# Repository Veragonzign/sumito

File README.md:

# sumito
Robot minisumo robtica tecnologia electrica

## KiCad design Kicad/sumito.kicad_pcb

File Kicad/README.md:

Esta carpeta contiene los archivos del esquema electrico y del diseño de la PCB del robot SUMITO.

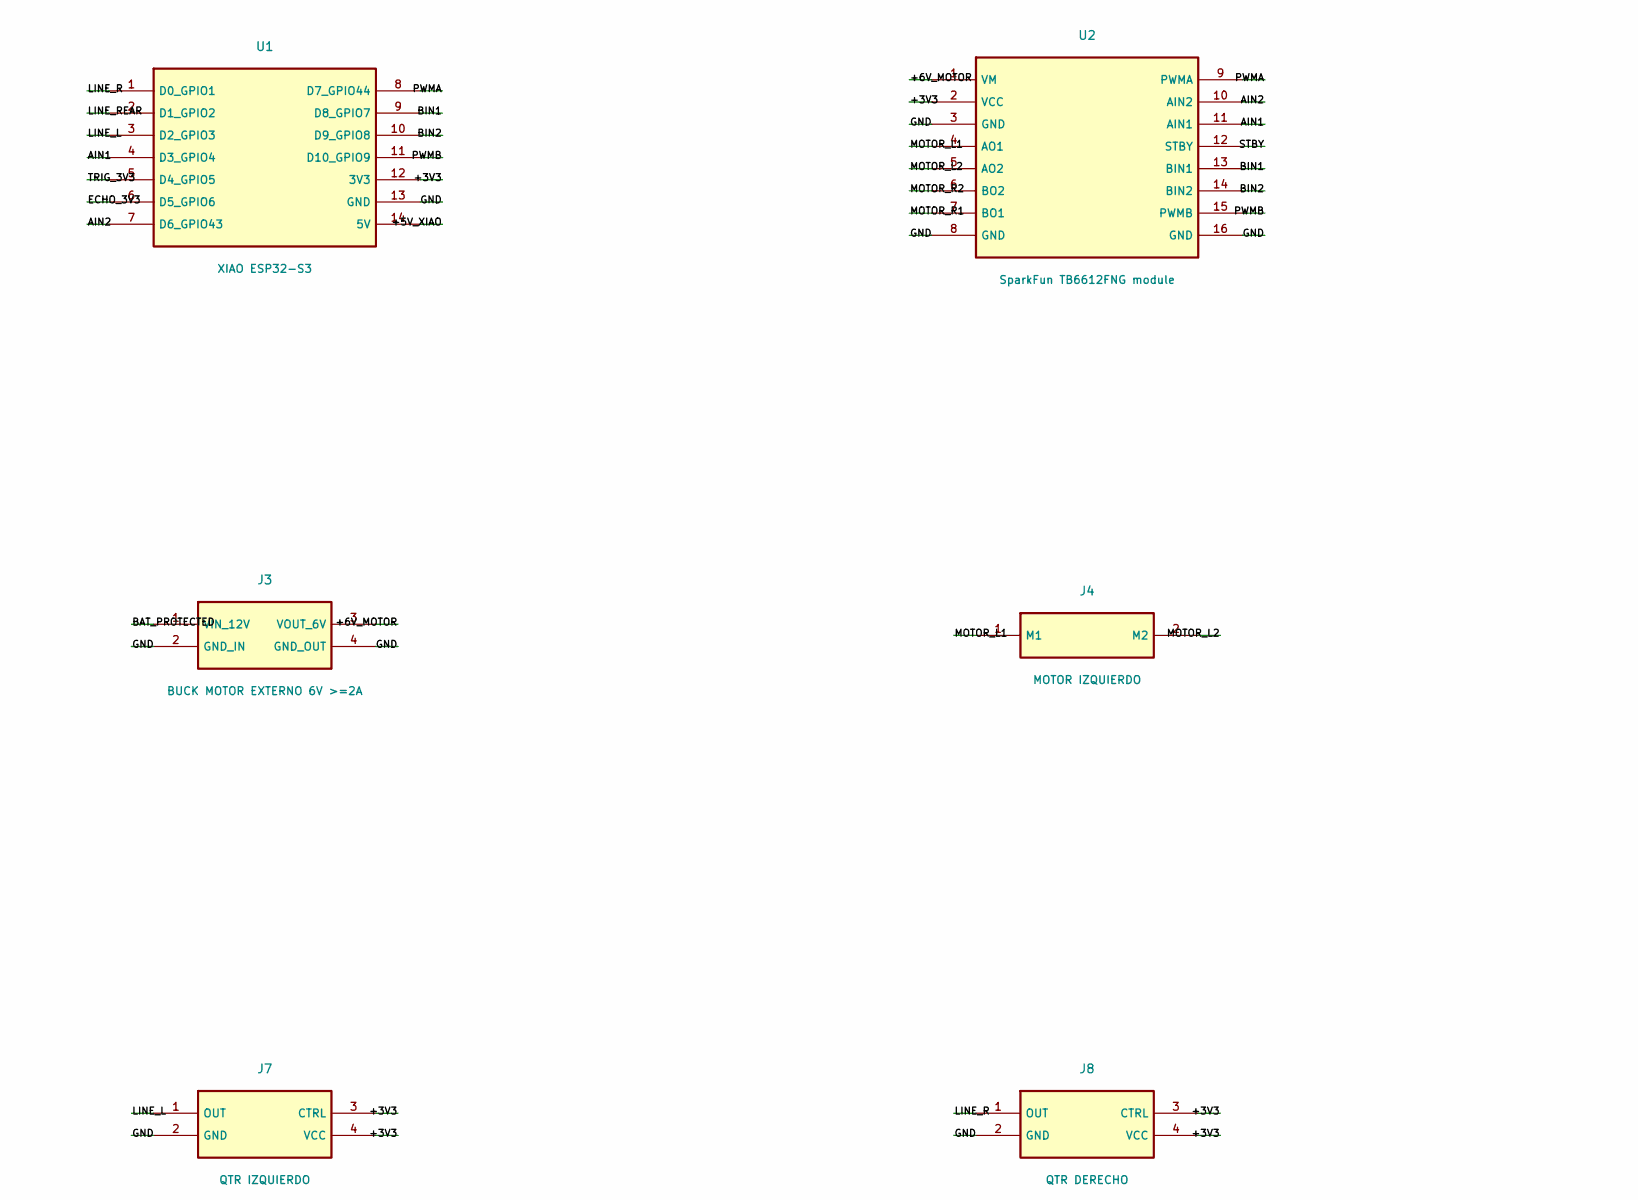
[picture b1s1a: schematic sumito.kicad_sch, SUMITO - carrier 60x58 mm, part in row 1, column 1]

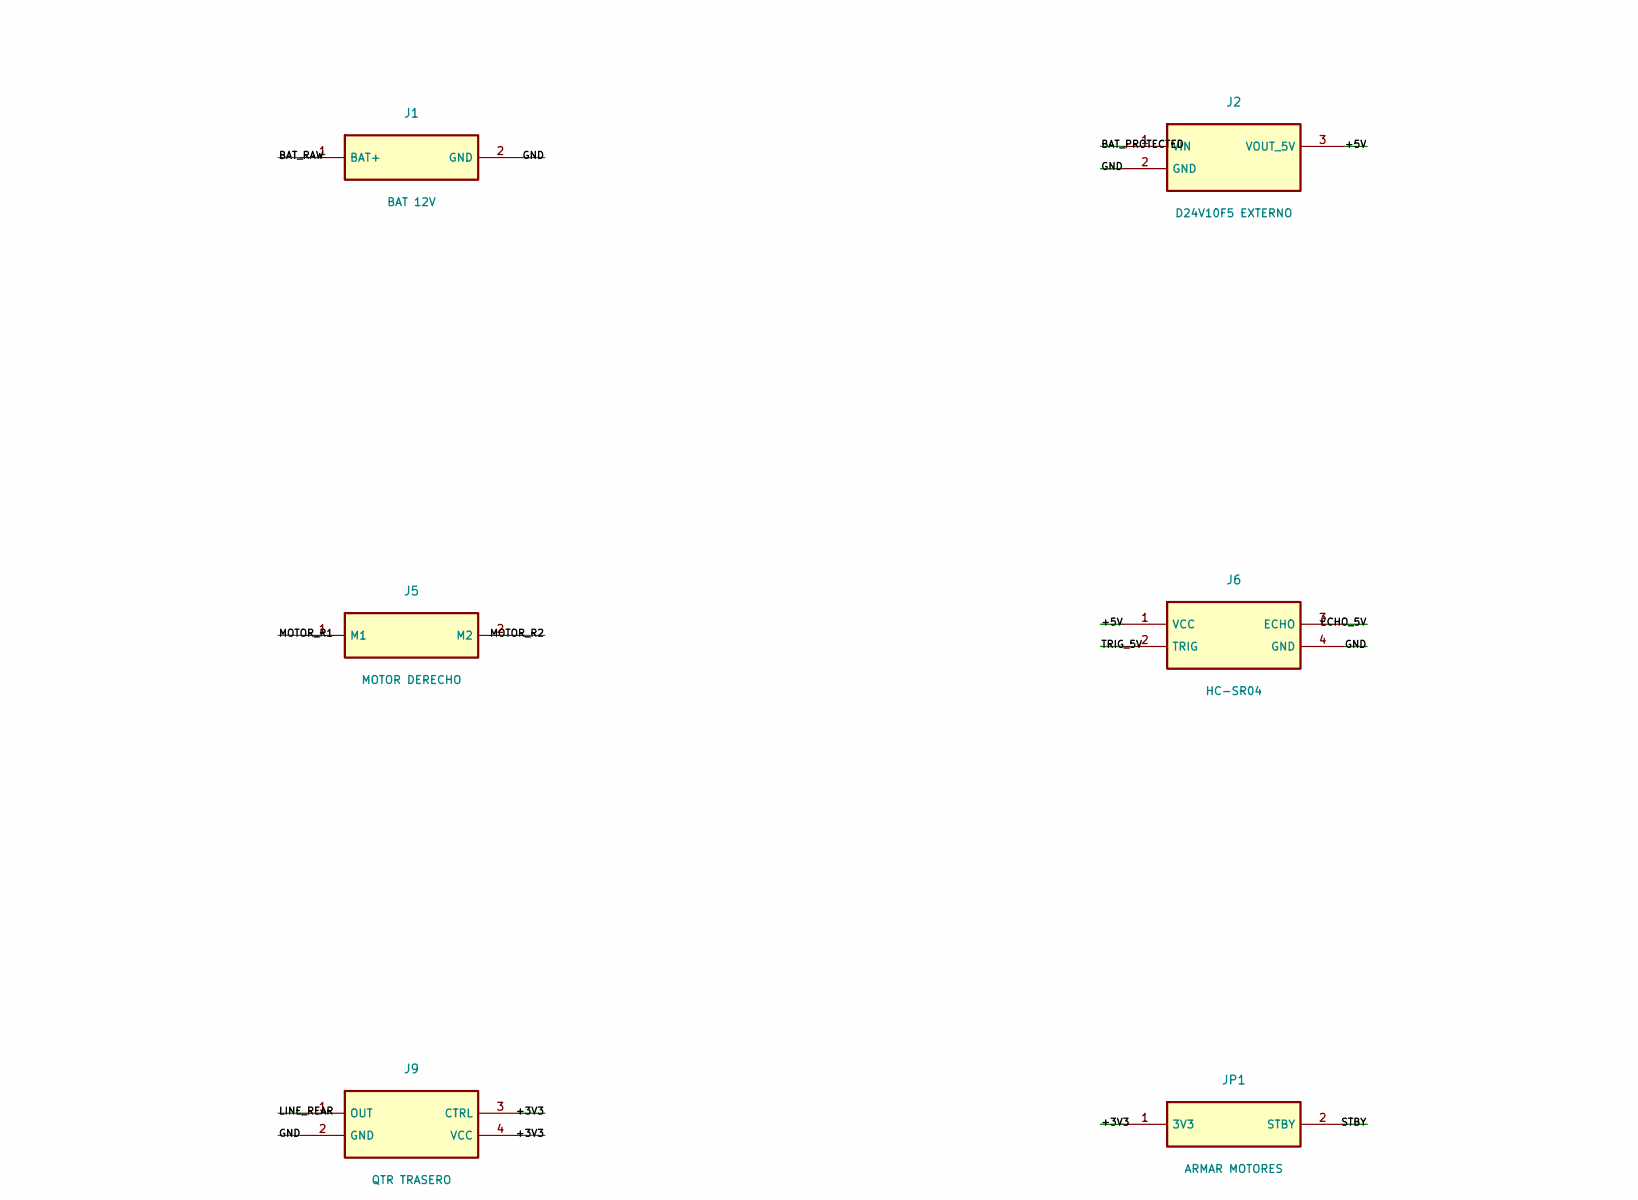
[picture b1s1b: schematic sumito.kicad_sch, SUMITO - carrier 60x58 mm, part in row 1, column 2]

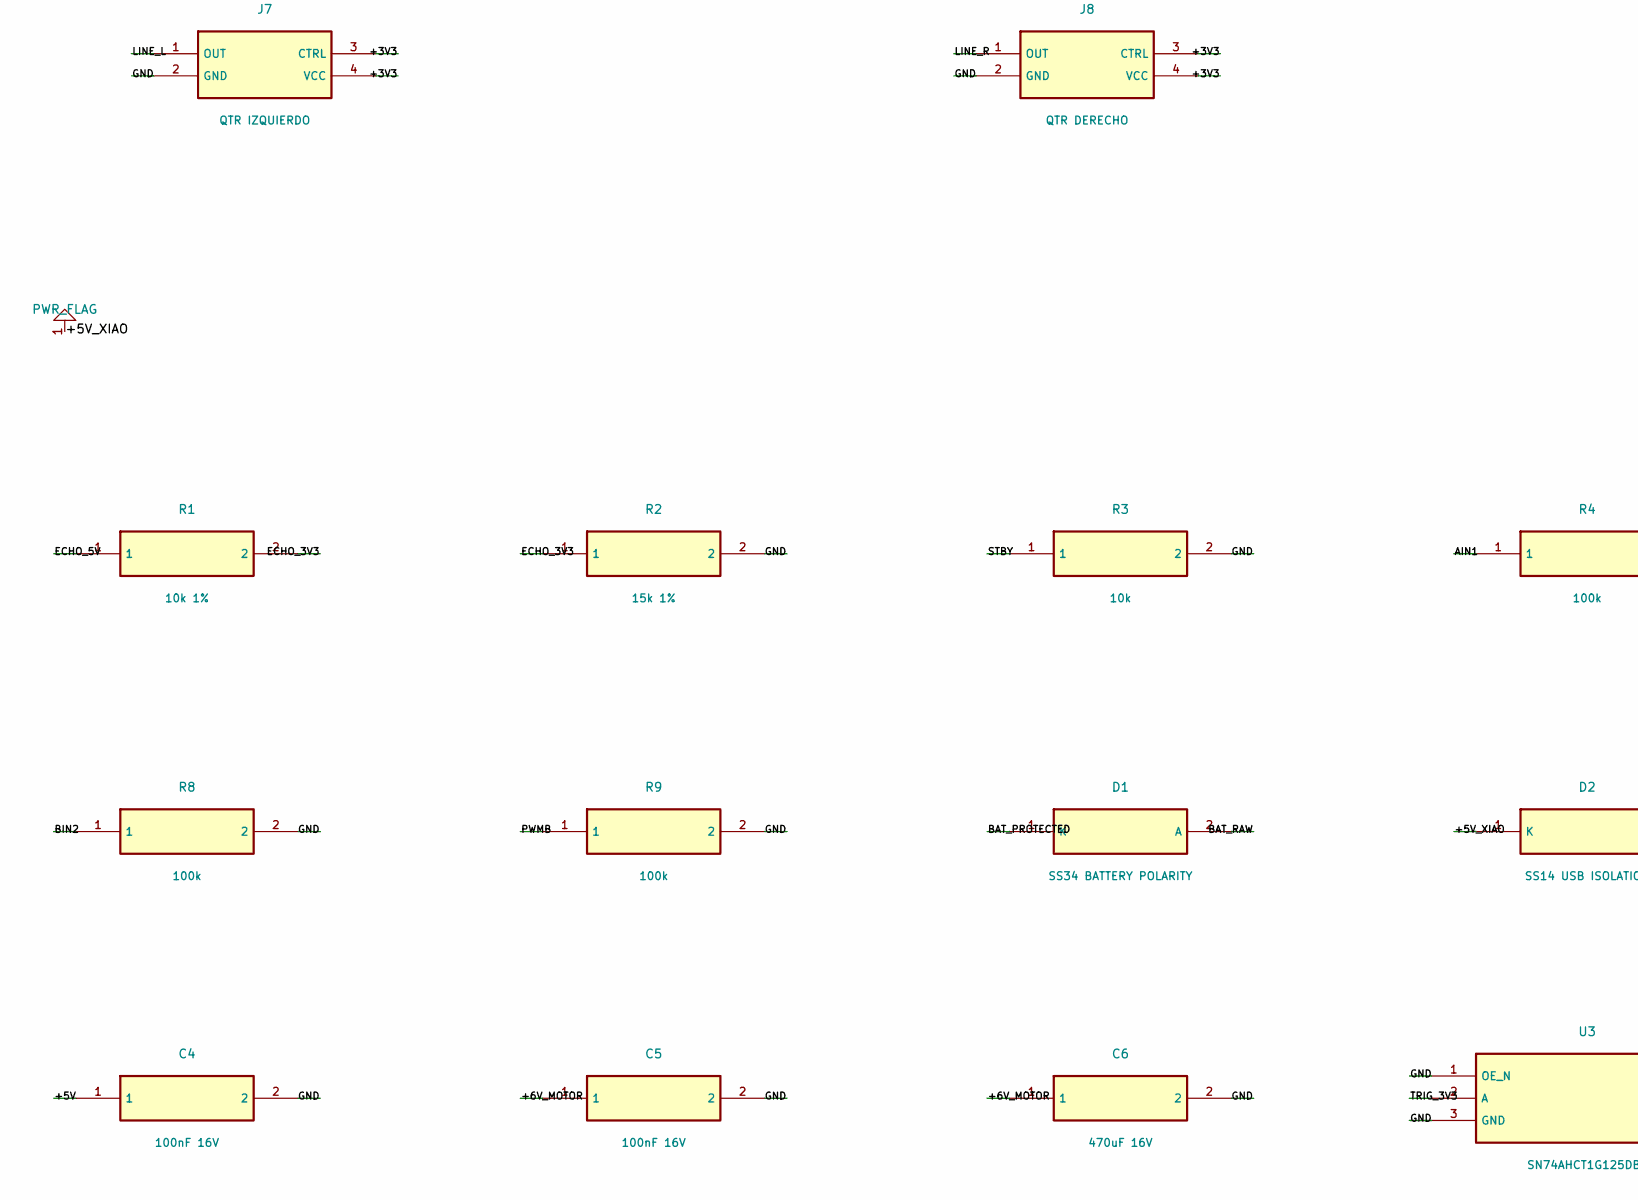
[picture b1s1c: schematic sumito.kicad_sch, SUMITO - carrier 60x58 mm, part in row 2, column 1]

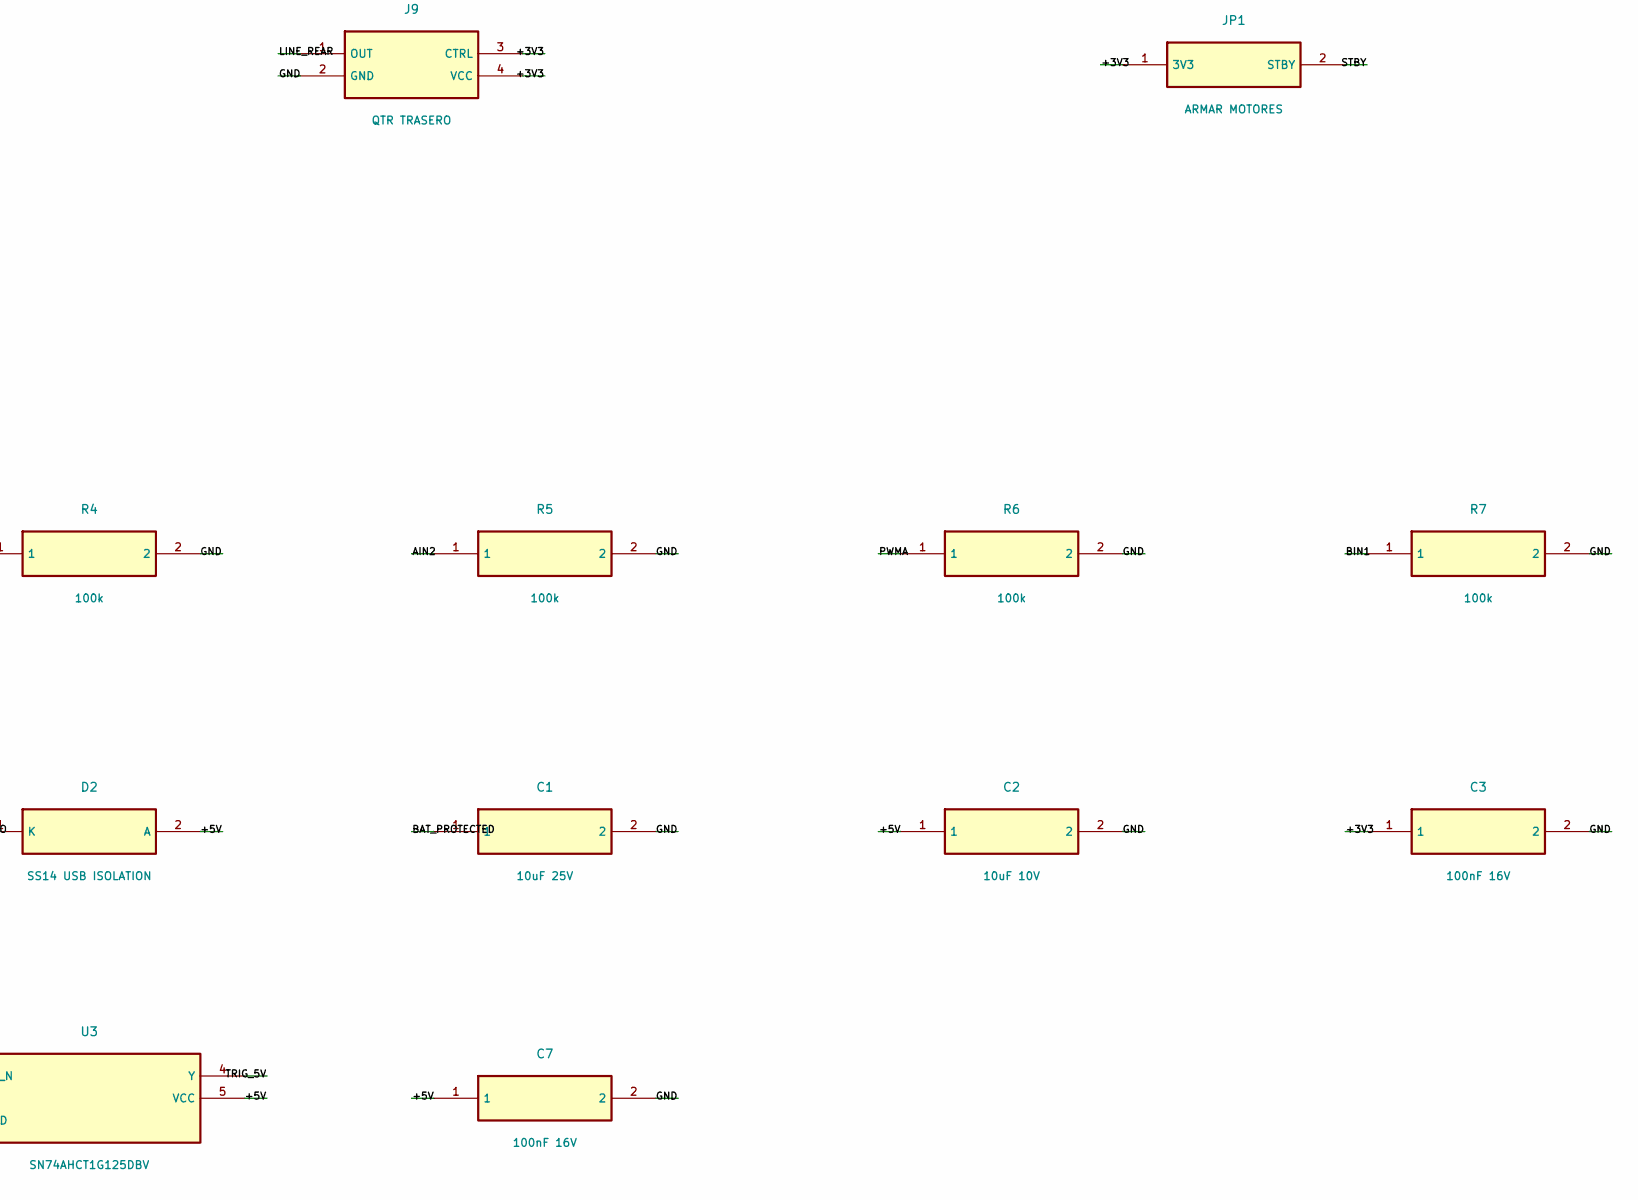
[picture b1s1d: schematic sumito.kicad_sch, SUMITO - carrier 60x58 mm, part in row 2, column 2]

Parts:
C1: 10uF 25V; C_0805_2012Metric
C2: 10uF 10V; C_0805_2012Metric
C3, C4, C5, C7: 100nF 16V; C_0805_2012Metric
C6: 470uF 16V; CP_Radial_D8.0mm_P3.50mm
D1: SS34 BATTERY POLARITY; D_SMA
D2: SS14 USB ISOLATION; D_SMA
J1: BAT 12V; Terminal_2P_5.08
J2: D24V10F5 EXTERNO; Header_1x3
J3: BUCK MOTOR EXTERNO 6V >=2A; Header_1x4
J4: MOTOR IZQUIERDO; Terminal_2P_5.08
J5: MOTOR DERECHO; Terminal_2P_5.08
J6: HC-SR04; Header_1x4
J7: QTR IZQUIERDO; Header_1x4
J8: QTR DERECHO; Header_1x4
J9: QTR TRASERO; Header_1x4
JP1: ARMAR MOTORES; Header_1x2
R1: 10k 1%; R_0805_2012Metric
R2: 15k 1%; R_0805_2012Metric
R3: 10k; R_0805_2012Metric
R4, R5, R6, R7, R8, R9: 100k; R_0805_2012Metric
U1: XIAO ESP32-S3; XIAO_ESP32S3_SOCKET
U2: SparkFun TB6612FNG module; SparkFun_TB6612FNG_SOCKET
U3: SN74AHCT1G125DBV; SOT-23-5

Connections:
/+3V3: C3.1, J7.3 (CTRL), J7.4 (VCC), J8.3 (CTRL), J8.4 (VCC), J9.3 (CTRL), J9.4 (VCC), JP1.1 (3V3), U1.12 (3V3), U2.2 (VCC)
/+5V: C2.1, C4.1, C7.1, D2.2 (A), J2.3 (VOUT_5V), J6.1 (VCC), U3.5 (VCC)
/+5V_XIAO: D2.1 (K), U1.14 (5V)
/+6V_MOTOR: C5.1, C6.1, J3.3 (VOUT_6V), U2.1 (VM)
/AIN1: R4.1, U1.4 (D3_GPIO4), U2.11 (AIN1)
/AIN2: R5.1, U1.7 (D6_GPIO43), U2.10 (AIN2)
/BAT_PROTECTED: C1.1, D1.1 (K), J2.1 (VIN), J3.1 (VIN_12V)
/BAT_RAW: D1.2 (A), J1.1 (BAT+)
/BIN1: R7.1, U1.9 (D8_GPIO7), U2.13 (BIN1)
/BIN2: R8.1, U1.10 (D9_GPIO8), U2.14 (BIN2)
/ECHO_3V3: R1.2, R2.1, U1.6 (D5_GPIO6)
/ECHO_5V: J6.3 (ECHO), R1.1
/GND: C1.2, C2.2, C3.2, C4.2, C5.2, C6.2, C7.2, J1.2 (GND), J2.2 (GND), J3.2 (GND_IN), J3.4 (GND_OUT), J6.4 (GND), J7.2 (GND), J8.2 (GND), J9.2 (GND), R2.2, R3.2, R4.2, R5.2, R6.2, R7.2, R8.2, R9.2, U1.13 (GND), U2.3 (GND), U2.8 (GND), U2.16 (GND), U3.1 (OE_N), U3.3 (GND)
/LINE_L: J7.1 (OUT), U1.3 (D2_GPIO3)
/LINE_R: J8.1 (OUT), U1.1 (D0_GPIO1)
/LINE_REAR: J9.1 (OUT), U1.2 (D1_GPIO2)
/MOTOR_L1: J4.1 (M1), U2.4 (AO1)
/MOTOR_L2: J4.2 (M2), U2.5 (AO2)
/MOTOR_R1: J5.1 (M1), U2.7 (BO1)
/MOTOR_R2: J5.2 (M2), U2.6 (BO2)
/PWMA: R6.1, U1.8 (D7_GPIO44), U2.9 (PWMA)
/PWMB: R9.1, U1.11 (D10_GPIO9), U2.15 (PWMB)
/STBY: JP1.2 (STBY), R3.1, U2.12 (STBY)
/TRIG_3V3: U1.5 (D4_GPIO5), U3.2 (A)
/TRIG_5V: J6.2 (TRIG), U3.4 (Y)

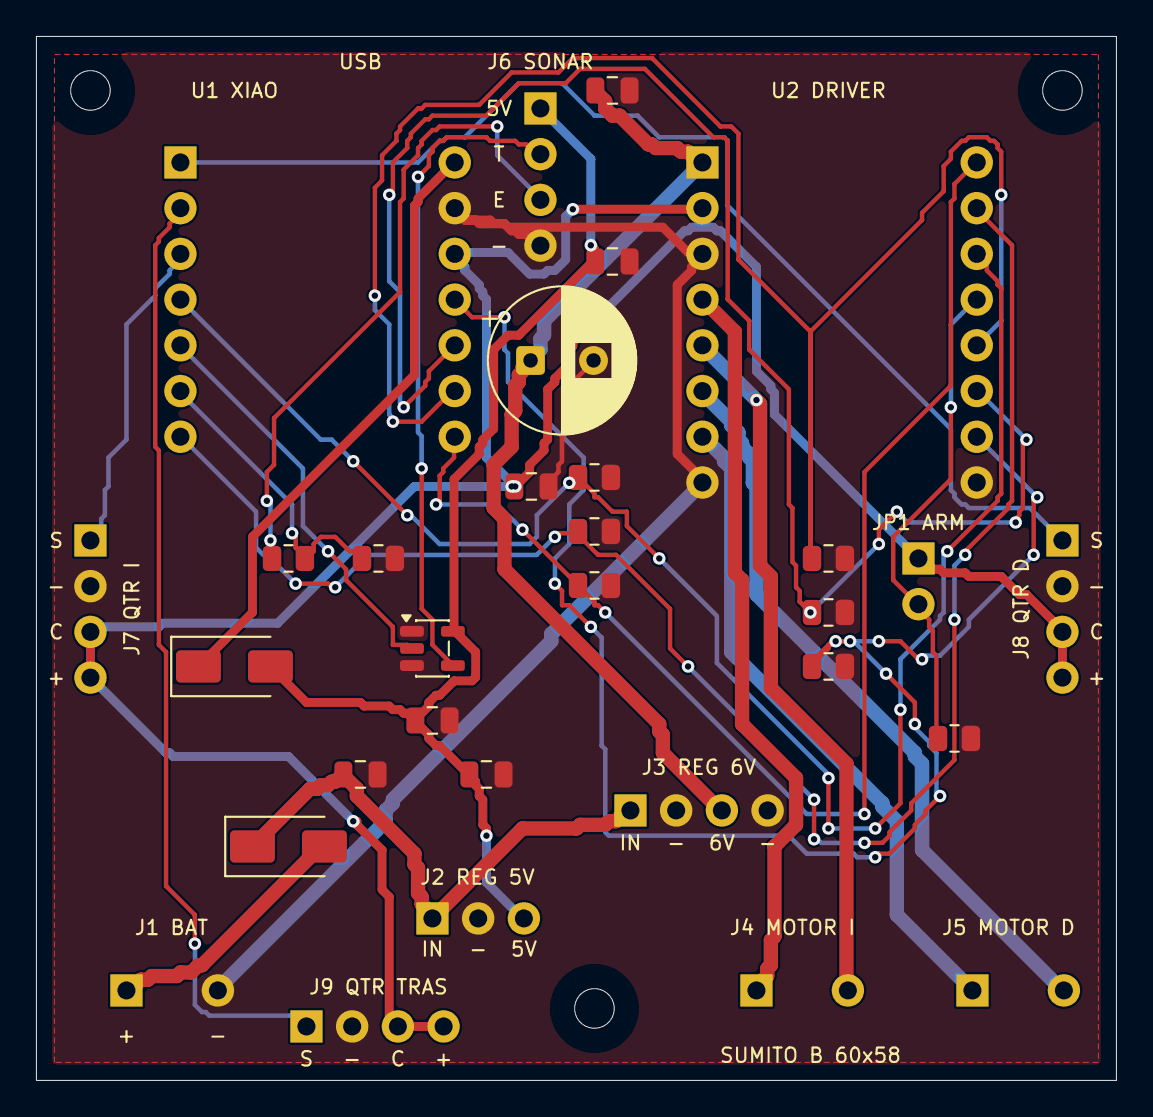
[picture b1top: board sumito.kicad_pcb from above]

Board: 2 copper layers, 60.0 x 58.0 mm, 34 parts (0 on the bottom side), 25 nets.

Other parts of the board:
H1, H2, H3: MountingHole_2.2mm_M2
